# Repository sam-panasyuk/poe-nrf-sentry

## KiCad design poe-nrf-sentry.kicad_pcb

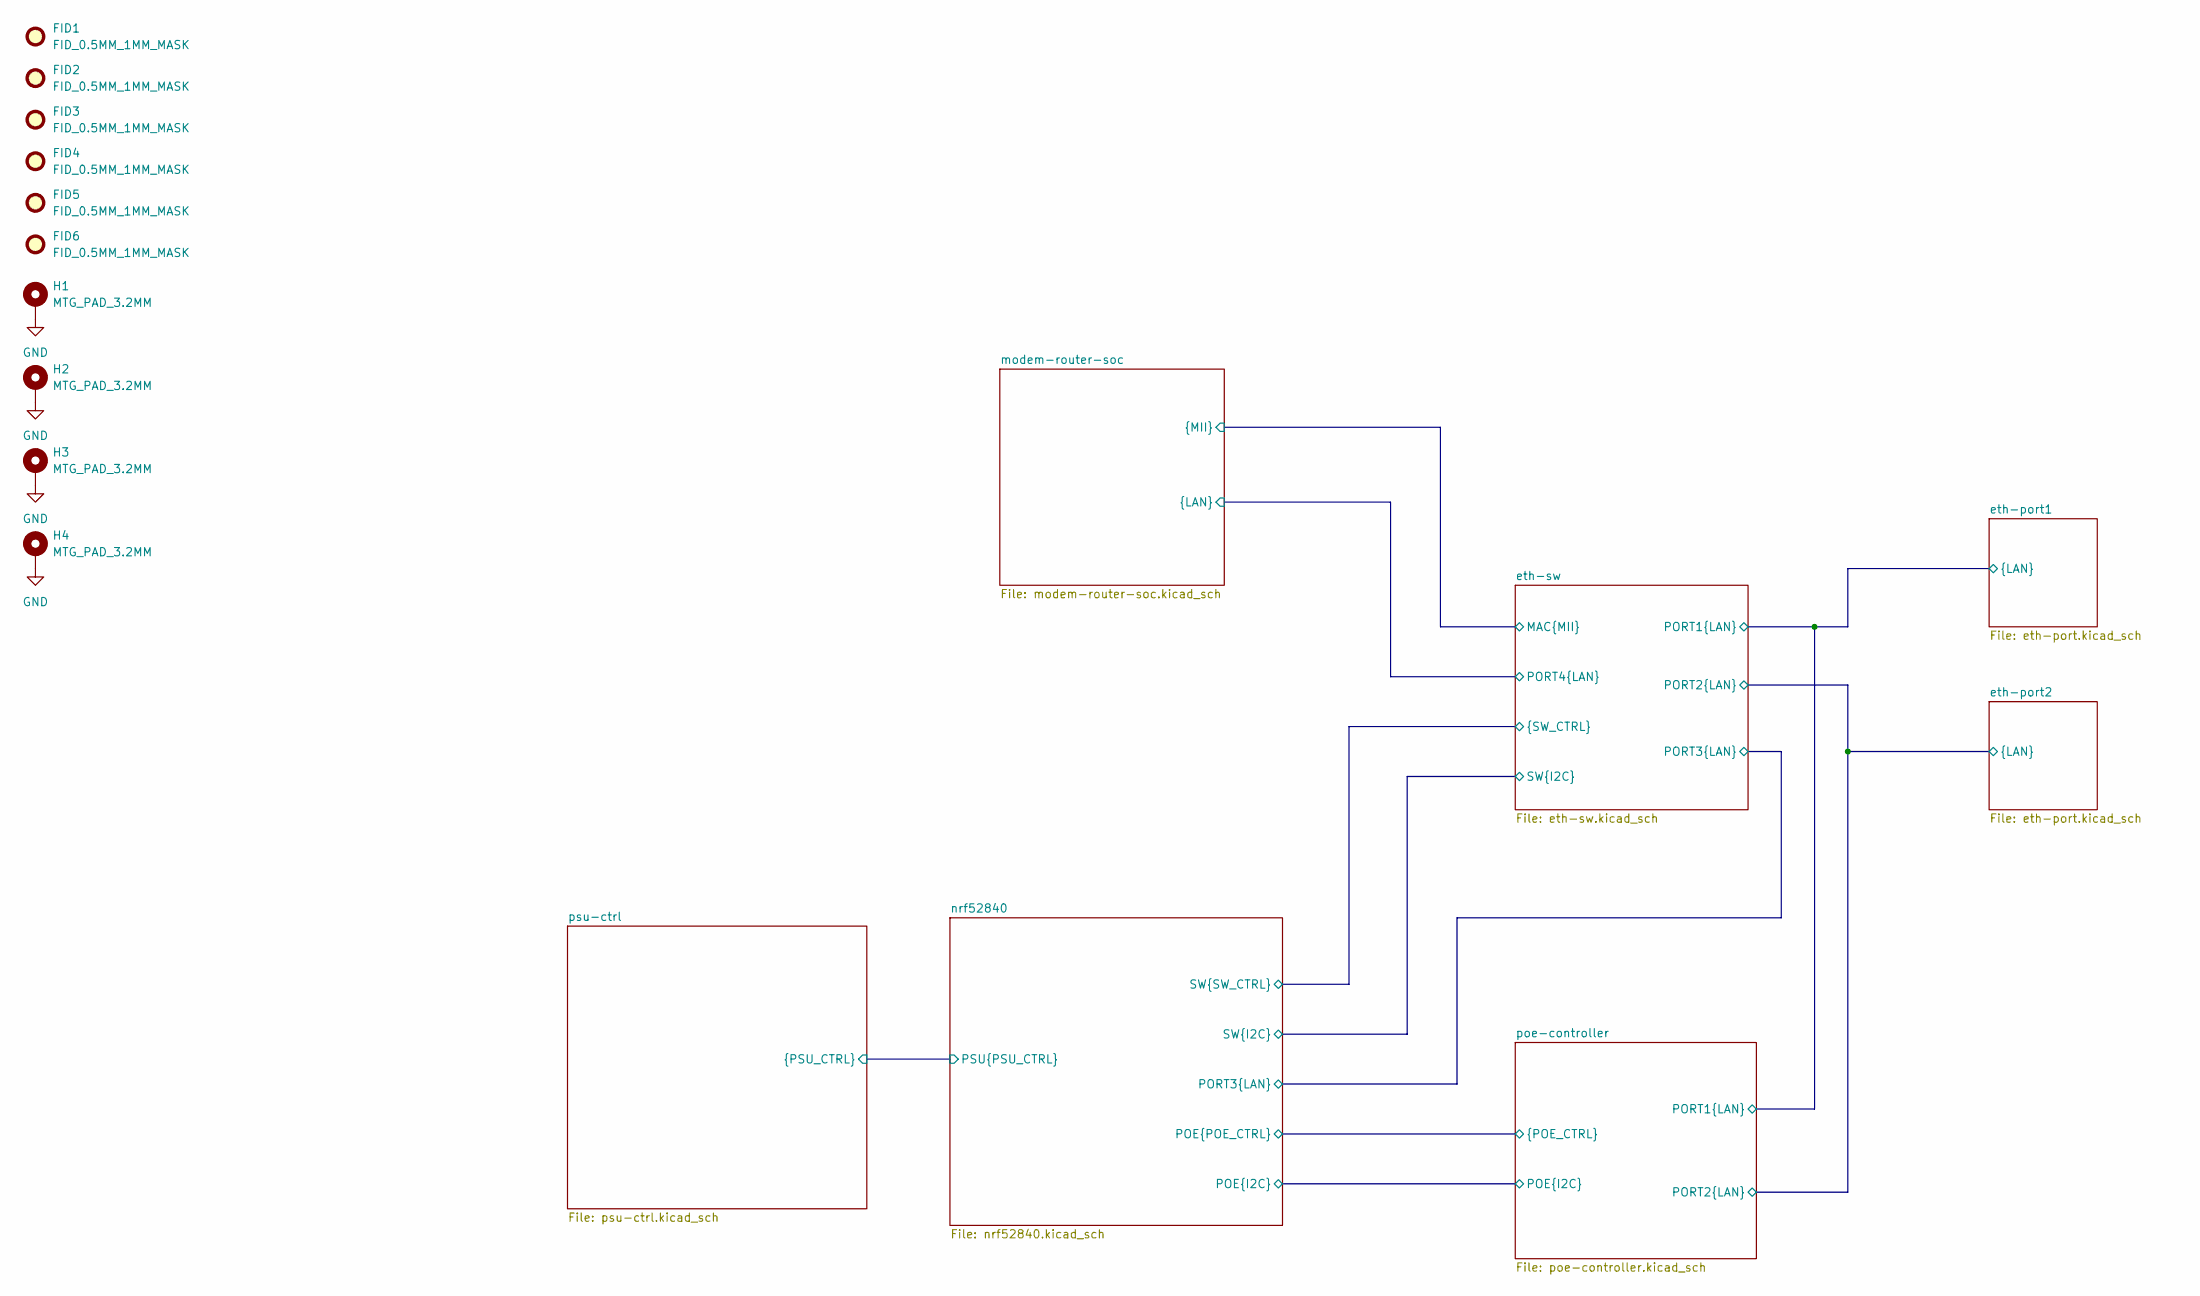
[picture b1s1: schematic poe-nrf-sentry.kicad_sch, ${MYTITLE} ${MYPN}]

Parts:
FID1, FID2, FID3, FID4, FID5, FID6: FID_0.5MM_1MM_MASK; Fiducial_0.5mm_Mask1mm
H1, H2, H3, H4: MTG_PAD_3.2MM; MountingHole_3.2mm_M3_Pad_TopBottom

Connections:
GND: H1.1 (1_1), H2.1 (1_1), H3.1 (1_1), H4.1 (1_1); also elsewhere on the board

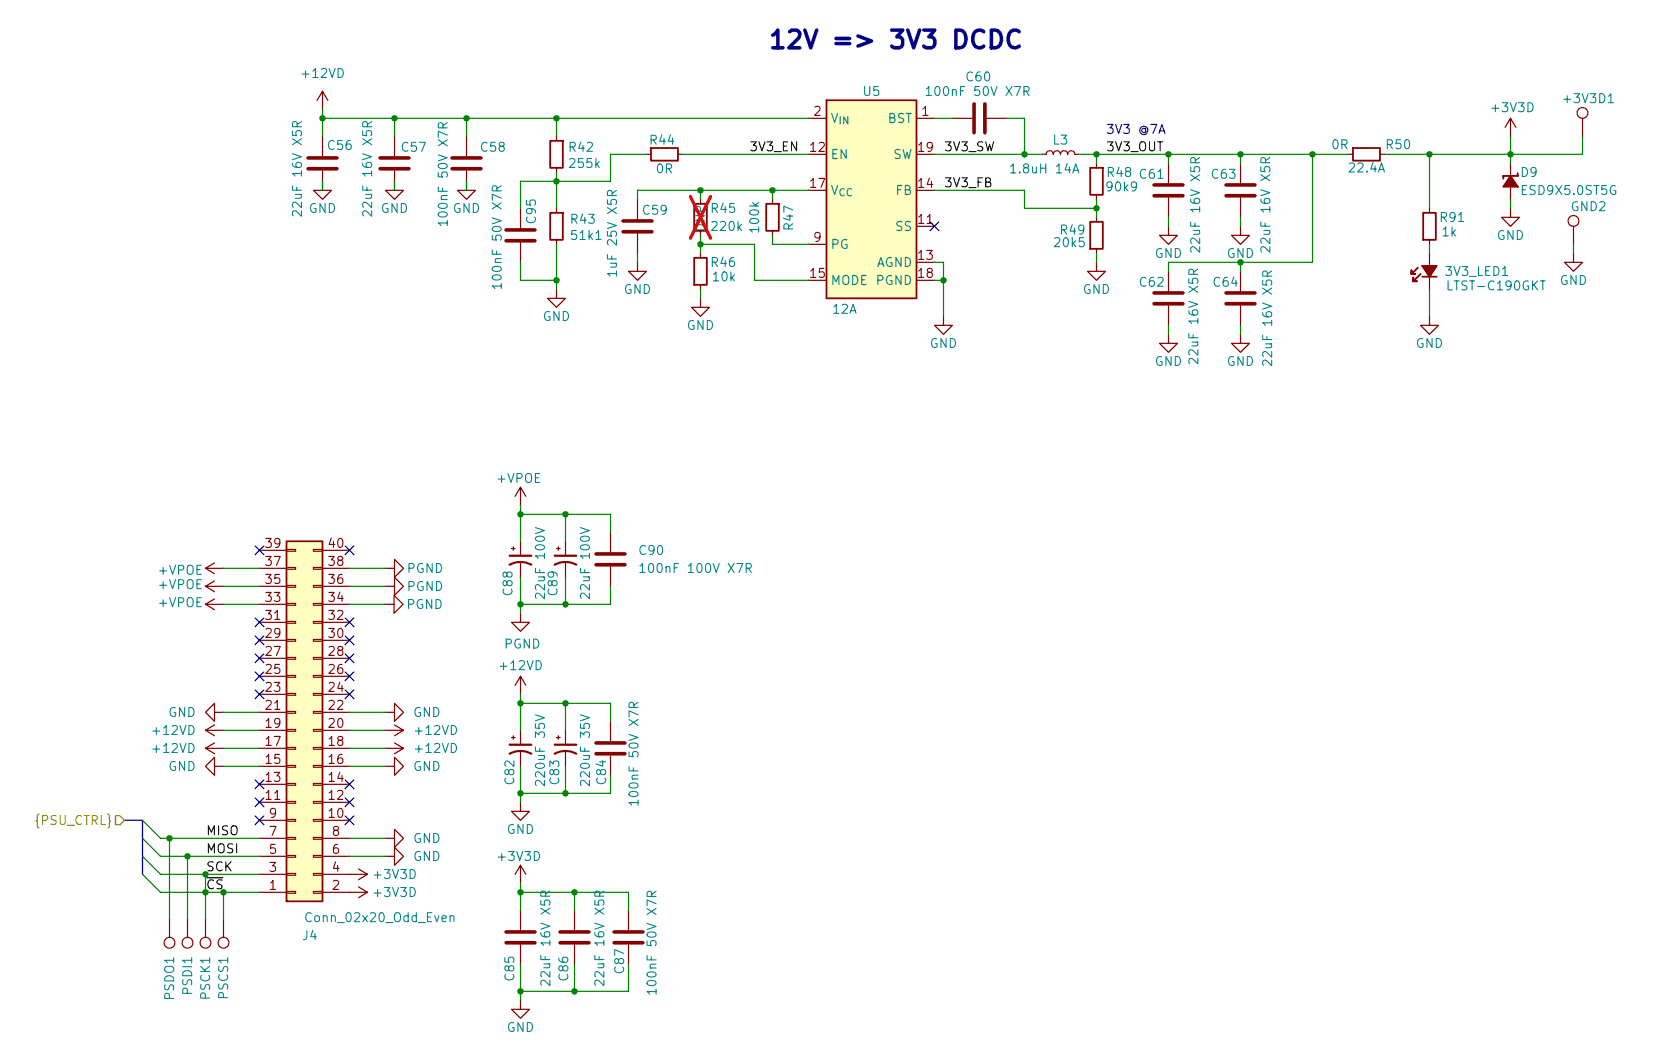
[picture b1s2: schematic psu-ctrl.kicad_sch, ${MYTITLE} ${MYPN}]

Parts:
3V3_LED1: LTST-C190GKT; LED_0603_1608Metric_G; MPN LTST-C190GKT
+3V3D1: TestPoint_1mm_0.5mm_TH; TestPoint_THTPad_D1.0mm_Drill0.5mm
C56, C57, C61, C62, C63, C64, C85, C86: 22uF 16V X5R; C_0603_1608Metric; MPN CL10A226MO7JZNC
C58, C60, C84, C87, C95: 100nF 50V X7R; C_0402_1005Metric; MPN CC0402KRX7R9BB104; JLCPN C131394
C59: 1uF 25V X5R; C_0402_1005Metric; MPN C1005X6S1A105K050BC
C82, C83: 220uF 35V; CP_Elec_8x10.5; MPN EMZA350ARA221MHA0G
C88, C89: 22uF 100V; CP_Elec_8x10.5; MPN UUX2A220MNL6GS
C90: 100nF 100V X7R; C_0603_1608Metric; MPN GRM188R72A104KA35D; JLCPN C113803
D9: ESD9X5.0ST5G; SOD-923; MPN ESD9X5.0ST5G
GND2: TestPoint_1mm_0.5mm_TH; TestPoint_THTPad_D1.0mm_Drill0.5mm
J4: Conn_02x20_Odd_Even; PinHeader_2x20_P2.54mm_Horizontal
L3: 1.8uH 14A; L_Coilcraft-XAL6030; MPN XAL6030-182MEC
PSCK1: TP 1mm; TestPoint_THTPad_D1.0mm_Drill0.5mm
PSCS1: TP 1mm; TestPoint_THTPad_D1.0mm_Drill0.5mm
PSDI1: TP 1mm; TestPoint_THTPad_D1.0mm_Drill0.5mm
PSDO1: TP 1mm; TestPoint_THTPad_D1.0mm_Drill0.5mm
R42: 255k; R_0402_1005Metric; MPN CR0402-FX-2553GLF
R43: 51k1; R_0402_1005Metric; MPN CR0402-FX-5112GLF
R44: 0R; R_0402_1005Metric; MPN ERJ2GE0R00X; JLCPN C17168
R45: R_220k_0402; R_0402_1005Metric; Tolerance 1%; MPN CR0402-FX-2203GLF; not fitted
R46: 10k; R_0402_1005Metric; MPN CR0402-FX-1002GLF; JLCPN C25744
R47: 100k; R_0402_1005Metric; MPN CRCW0402100KFKED
R48: 90k9; R_0402_1005Metric; MPN CR0402-FX-9092GLF
R49: 20k5; R_0402_1005Metric; MPN CRCW040220K0FKED
R50: R_0R_22.4A_0603; R_0603_1608Metric; Tolerance template_tolerance; MPN PMR03EZPJ000
R91: 1k; R_0402_1005Metric; MPN CR0402-FX-1001GLF
U5: 12A; QFN-20-1EP_3x3mm_P0.45mm_TPS56xxxx; MPN TPS56C230RJER

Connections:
+3V3D: +3V3D1.1 (1_1), C85.1, C86.1, C87.1, D9.1 (C), J4.2, J4.4, R50.2, R91.2; also elsewhere on the board
+12VD: C56.2, C57.2, C58.1, C82.1, C83.1, C84.1, J4.17, J4.18, J4.19, J4.20, R42.1, U5.2 (V_{IN}), U5.3 (V_{IN}), U5.4 (V_{IN}), U5.5 (V_{IN}); also elsewhere on the board
+VPOE: C88.1, C89.1, C90.1, J4.33, J4.35, J4.37; also elsewhere on the board
/eth-sw/MISO: J4.7, PSDO1.1 (1_1); also elsewhere on the board
/eth-sw/MOSI: J4.5, PSDI1.1 (1_1); also elsewhere on the board
/psu-ctrl/3V3_EN: R44.2, U5.12 (EN)
/psu-ctrl/3V3_FB: R48.2, R49.2, U5.14 (FB)
/psu-ctrl/3V3_OUT: C61.2, C62.2, C63.2, C64.2, L3.2, R48.1, R50.1
/psu-ctrl/3V3_SW: C60.1, L3.1, U5.6 (SW), U5.19 (SW), U5.20 (SW)
GND: 3V3_LED1.1 (C), C56.1, C57.1, C58.2, C59.1, C61.1, C62.1, C63.1, C64.1, C82.2, C83.2, C84.2, C85.2, C86.2, C87.2, C95.2, D9.2 (A), GND2.1 (1_1), J4.6, J4.8, J4.15, J4.16, J4.21, J4.22, R43.2, R46.1, R49.1, U5.7 (PGND), U5.8 (PGND), U5.13 (AGND), U5.18 (PGND), U5.21 (PGND); also elsewhere on the board
unnamed: 3V3_LED1.2 (A), R91.1
unnamed: C95.1, R42.2, R43.1, R44.1
unnamed: C60.2, U5.1 (BST)
unnamed: R45.1, R46.2, U5.15 (MODE)
unnamed: R47.2, U5.9 (PG)
unnamed: C59.2, R45.2, R47.1, U5.17 (V_{CC})
PGND: C88.2, C89.2, C90.2, J4.34, J4.36, J4.38; also elsewhere on the board

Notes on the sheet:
12V => 3V3 DCDC
3V3 @7A

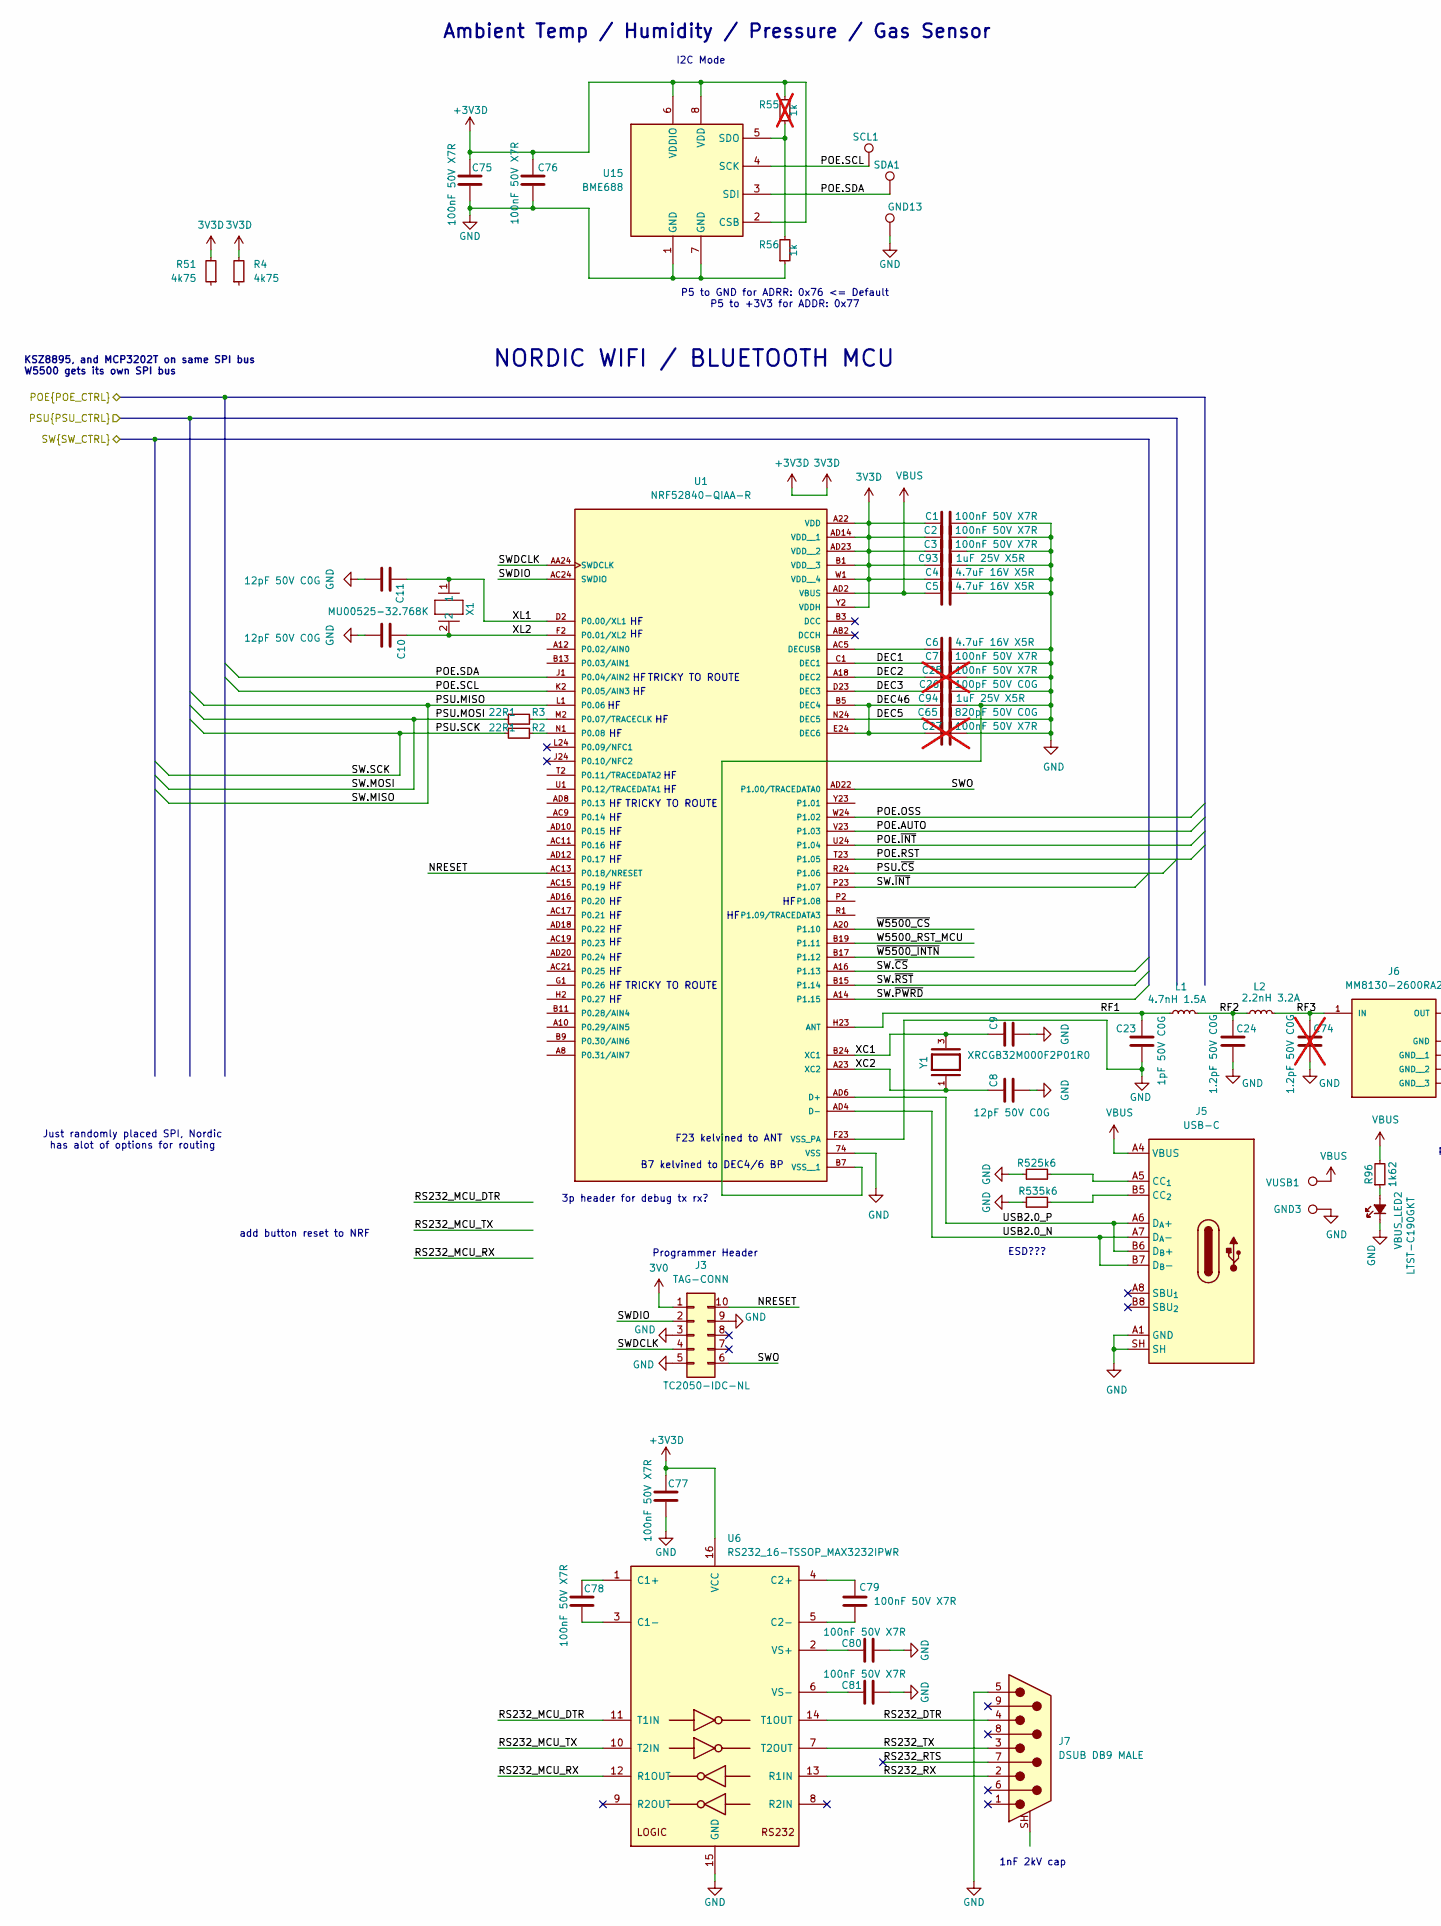
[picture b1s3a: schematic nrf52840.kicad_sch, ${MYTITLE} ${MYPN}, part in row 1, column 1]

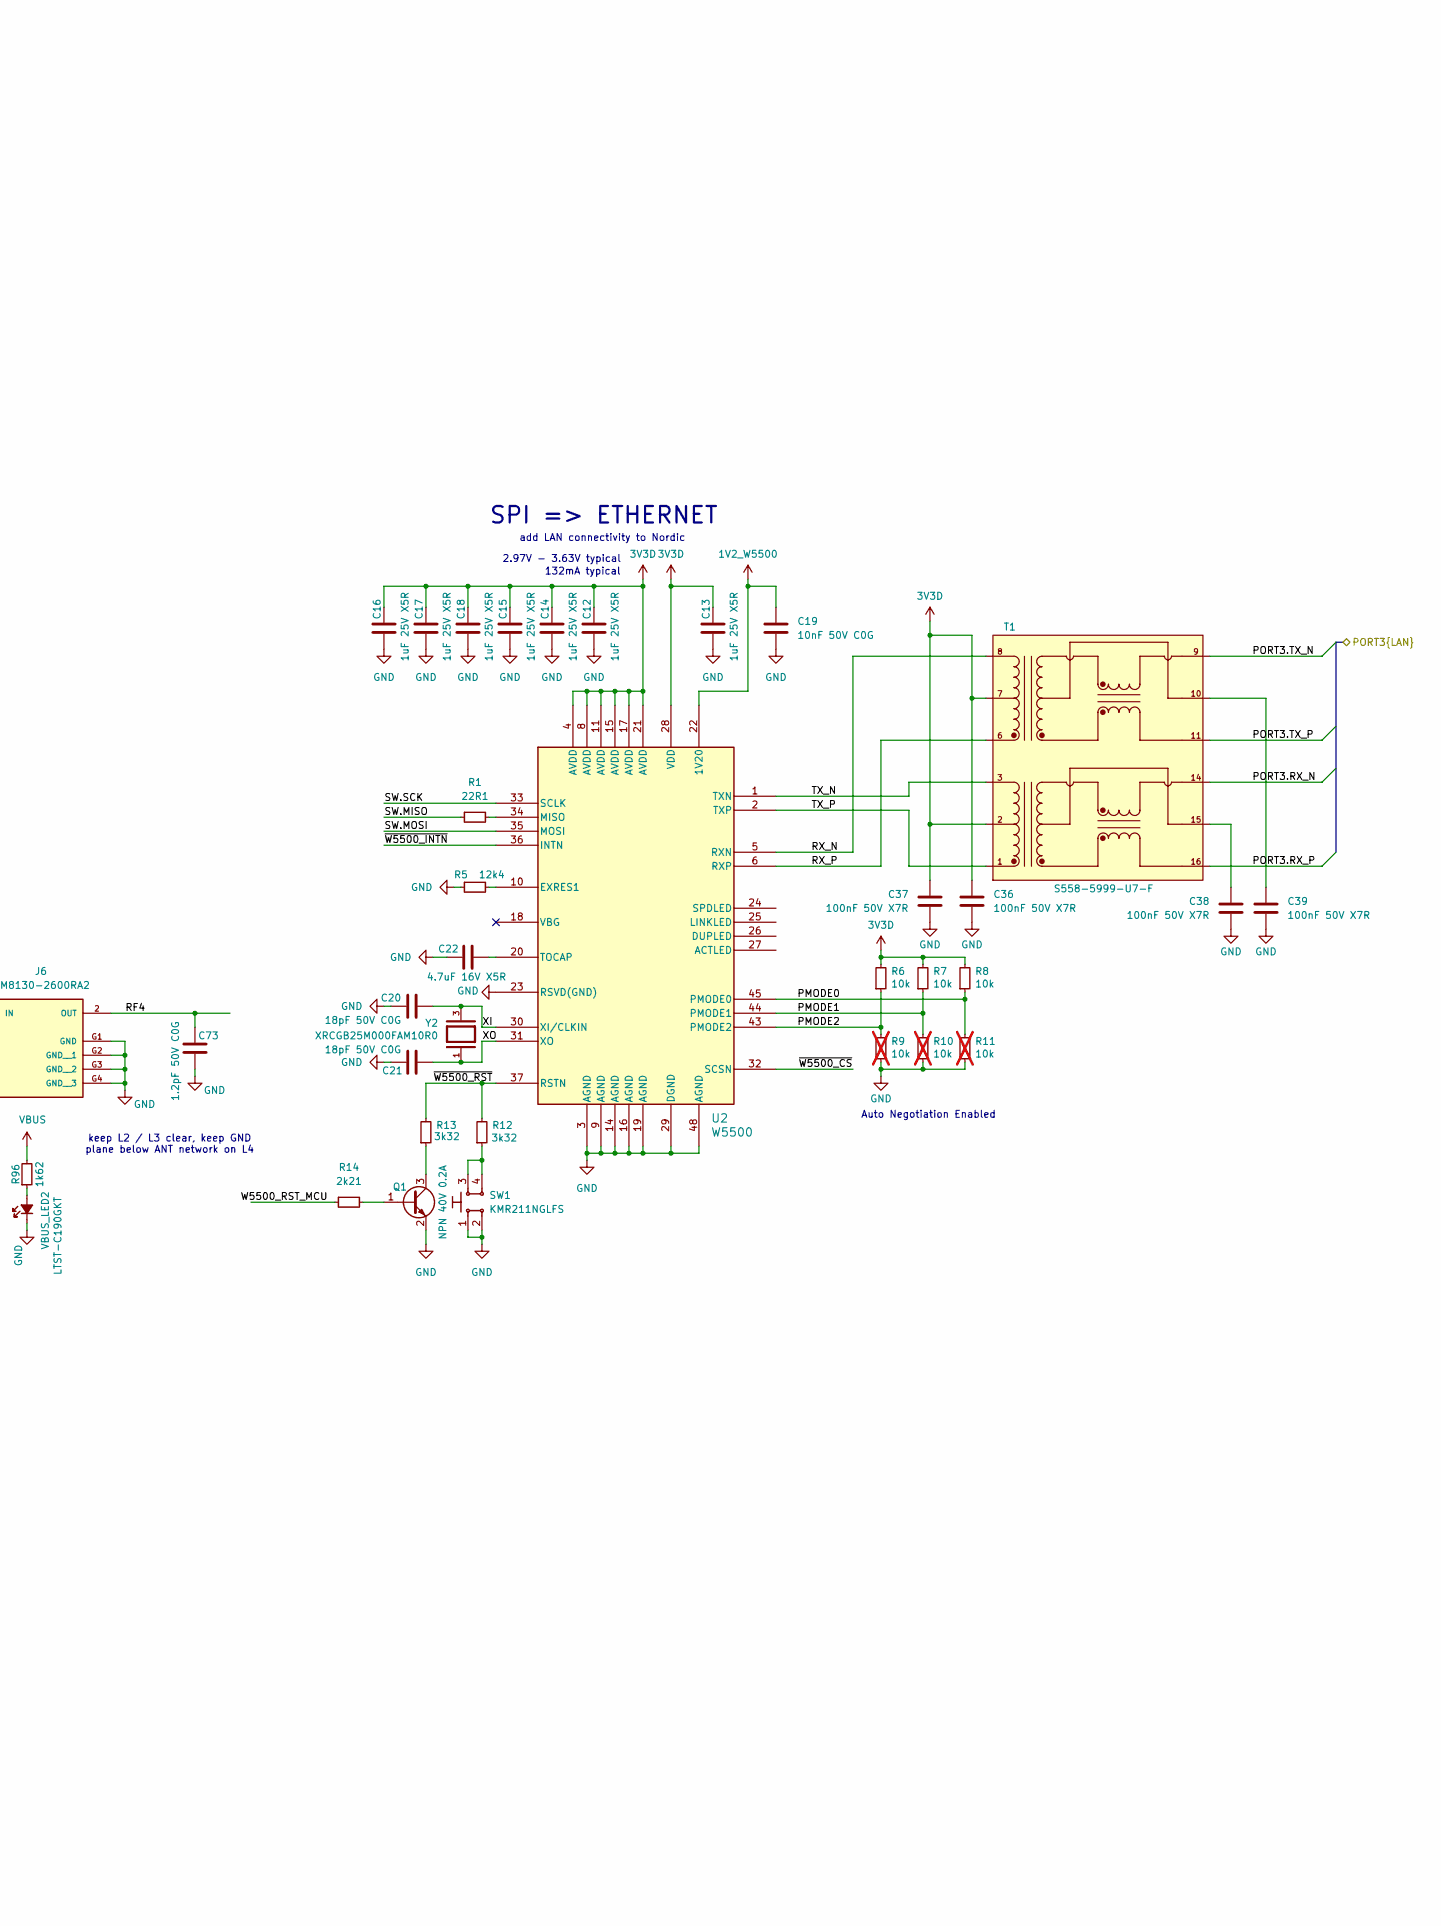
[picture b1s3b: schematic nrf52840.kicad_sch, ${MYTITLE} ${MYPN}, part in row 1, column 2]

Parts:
C1, C2, C3, C7, C36, C37, C38, C39, C75, C76, C77, C78, C79, C80, C81: 100nF 50V X7R; C_0402_1005Metric; MPN CC0402KRX7R9BB104; JLCPN C131394
C4, C5, C6, C22: 4.7uF 16V X5R; C_0402_1005Metric
C8, C9, C10, C11: 12pF 50V C0G; C_0402_1005Metric
C12, C13, C14, C15, C16, C17, C18, C93, C94: 1uF 25V X5R; C_0402_1005Metric; JLCPN C52923
C19: 10nF 50V C0G; C_0603_1608Metric
C20, C21: 18pF 50V C0G; C_0402_1005Metric
C23: 1pF 50V C0G; C_0402_1005Metric
C24, C73: 1.2pF 50V C0G; C_0402_1005Metric
C25, C27: 100nF 50V X7R; C_0402_1005Metric; MPN CC0402KRX7R9BB104; JLCPN C131394; not fitted
C26: 100pF 50V C0G; C_0402_1005Metric
C65: 820pF 50V C0G; C_0402_1005Metric
C74: 1.2pF 50V C0G; C_0402_1005Metric; not fitted
GND3: TestPoint_1.5mm_0.7mm_TH; TestPoint_THTPad_D1.5mm_Drill0.7mm
GND13: TestPoint_1mm_0.5mm_TH; TestPoint_THTPad_D1.0mm_Drill0.5mm
J3: TAG-CONN; Tag-Connect_TC2050-IDC-NL_2x5_P1.27mm; MPN TC2050-IDC-NL
J5: USB-C; USB-C_Receptacle_GCT_USB4105-GF-A; MPN USB4105-GF-A; JLCPN C5184243
J6: MM8130-2600RA2; MURATA_MM8130-2600RA2; MPN MM8130-2600RA2; JLCPN C167503
J7: DSUB DB9 MALE; DSUB-9_Pins_Horizontal_P2.77x2.84mm_EdgePinOffset7.70mm_Hou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; MPN A-DS 09 A/KG-T2S; JLCPN C7498157
L1: 4.7nH 1.5A; L_0603_1608Metric; MPN LQW18AN4N7B80D
L2: 2.2nH 3.2A; L_0603_1608Metric; MPN LQW18AN2N2C80D
Q1: NPN 40V 0.2A; SOT-323_SC-70; MPN MMBT3904WT1G; JLCPN C58011
R1, R2, R3: 22R1; R_0402_1005Metric; JLCPN C59651
R4, R51: 4k75; R_0402_1005Metric
R5: 12k4; R_0402_1005Metric
R6, R7, R8: 10k; R_0402_1005Metric; MPN CR0402-FX-1002GLF; JLCPN C25744
R9, R10, R11: 10k; R_0402_1005Metric; MPN CR0402-FX-1002GLF; JLCPN C25744; not fitted
R12, R13: 3k32; R_0402_1005Metric; JLCPN C60075
R14: 2k21; R_0402_1005Metric; JLCPN C324924
R52, R53: 5k6; R_0402_1005Metric; MPN RC0402FR-075K6L; JLCPN C25908
R55: 1k; R_0402_1005Metric; MPN CR0402-FX-1001GLF; not fitted
R56: 1k; R_0402_1005Metric; MPN CR0402-FX-1001GLF
R96: 1k62; R_0402_1005Metric; JLCPN C138038
SCL1: TestPoint_1mm_0.5mm_TH; TestPoint_THTPad_D1.0mm_Drill0.5mm
SDA1: TestPoint_1mm_0.5mm_TH; TestPoint_THTPad_D1.0mm_Drill0.5mm
SW1: SW_KMR211NGLFS_SMD; MPN KMR211NGLFS
T1: S558-5999-U7-F; Transformer_Ethernet_CNDtek_H1102N; MPN S558-5999-U7-F; JLCPN C6801130
U1: NRF52840-QIAA-R; XCVR_NRF52840-QIAA-R; MPN NRF52840-QIAA-R; JLCPN C190794
U2: W5500; LQFP-48_7x7mm_P0.5mm; MPN W5500; JLCPN C32843
U6: RS232_16-TSSOP_MAX3232IPWR; TSSOP-16_4.4x5mm_P0.65mm; MPN MAX3232IPWR; JLCPN C113205
U15: BME688; Bosch_LGA-8_3x3mm_P0.8mm_ClockwisePinNumbering; MPN BME688
VBUS_LED2: LTST-C190GKT; LED_0603_1608Metric_G; MPN LTST-C190GKT; JLCPN C125093
VUSB1: TestPoint_1.5mm_0.7mm_TH; TestPoint_THTPad_D1.5mm_Drill0.7mm
X1: MU00525-32.768K; XTAL_MU00525_NDK; MPN MU00525-32.768K
Y1: XRCGB32M000F2P01R0; XRCGB25M000FAM10R0; MPN XRCGB32M000F2P01R0; JLCPN C1985928
Y2: XRCGB25M000FAM10R0; MPN XRCGB25M000FAM10R0

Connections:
1V2_W5500: C19.1, U2.22 (1V20)
3V0: J3.1
+3V3D: C1.1, C2.1, C3.1, C4.1, C12.1, C13.1, C14.1, C15.1, C16.1, C17.1, C18.1, C36.1, C37.1, C75.2, C76.2, C77.2, C93.1, R4.2, R6.2, R7.2, R8.2, R51.2, R55.2, T1.2, T1.7, U1.A22 (VDD), U1.AD14 (VDD__1), U1.AD23 (VDD__2), U1.B1 (VDD__3), U1.W1 (VDD__4), U1.Y2 (VDDH), U2.4 (AVDD), U2.8 (AVDD), U2.11 (AVDD), U2.15 (AVDD), U2.17 (AVDD), U2.21 (AVDD), U2.28 (VDD), U6.16 (VCC), U15.2 (CSB), U15.6 (VDDIO), U15.8 (VDD); also elsewhere on the board
/eth-sw/MISO: R1.1, U1.L1 (P0.06); also elsewhere on the board
/eth-sw/MOSI: R2.1, U2.35 (MOSI); also elsewhere on the board
/eth-sw/PORT3.RX_N: T1.14; also elsewhere on the board
/eth-sw/PORT3.RX_P: T1.16; also elsewhere on the board
/eth-sw/PORT3.TX_N: T1.9; also elsewhere on the board
/eth-sw/PORT3.TX_P: T1.11; also elsewhere on the board
/eth-sw/~CS: U1.A16 (P1.13); also elsewhere on the board
/eth-sw/~INT: U1.P23 (P1.07); also elsewhere on the board
/eth-sw/~PWRD: U1.A14 (P1.15); also elsewhere on the board
/eth-sw/~RST: U1.B15 (P1.14); also elsewhere on the board
/nrf52840/DEC1: C7.1, U1.C1 (DEC1)
/nrf52840/DEC2: C25.1, U1.A18 (DEC2)
/nrf52840/DEC3: C26.1, U1.D23 (DEC3)
/nrf52840/DEC5: C65.1, U1.N24 (DEC5)
/nrf52840/DEC46: C27.1, C94.1, U1.B5 (DEC4), U1.E24 (DEC6)
/nrf52840/NRESET: J3.10, U1.AC13 (P0.18/NRESET)
/nrf52840/PMODE0: R8.1, R11.2, U2.45 (PMODE0)
/nrf52840/PMODE1: R7.1, R10.2, U2.44 (PMODE1)
/nrf52840/PMODE2: R6.1, R9.2, U2.43 (PMODE2)
/nrf52840/POE.AUTO: U1.V23 (P1.03); also elsewhere on the board
/nrf52840/POE.OSS: U1.W24 (P1.02); also elsewhere on the board
/nrf52840/POE.RST: U1.T23 (P1.05); also elsewhere on the board
/nrf52840/POE.SCL: SCL1.1 (1_1), U1.K2 (P0.05/AIN3), U15.4 (SCK); also elsewhere on the board
/nrf52840/POE.SDA: SDA1.1 (1_1), U1.J1 (P0.04/AIN2), U15.3 (SDI); also elsewhere on the board
/nrf52840/POE.~INT: U1.U24 (P1.04); also elsewhere on the board
/nrf52840/RF1: C23.1, L1.1, U1.H23 (ANT)
/nrf52840/RF2: C24.1, L1.2, L2.1
/nrf52840/RF3: C74.1, J6.1 (IN), L2.2
/nrf52840/RF4: C73.1, J6.2 (OUT)
/nrf52840/RS232_DTR: J7.4, U6.14 (T1OUT)
/nrf52840/RS232_MCU_DTR: U6.11 (T1IN)
/nrf52840/RS232_MCU_RX: U6.12 (R1OUT)
/nrf52840/RS232_MCU_TX: U6.10 (T2IN)
/nrf52840/RS232_RTS: J7.7
/nrf52840/RS232_RX: J7.2, U6.13 (R1IN)
/nrf52840/RS232_TX: J7.3, U6.7 (T2OUT)
/nrf52840/RX_N: T1.8, U2.5 (RXN)
/nrf52840/RX_P: T1.6, U2.6 (RXP)
/nrf52840/SWDCLK: J3.4, U1.AA24 (SWDCLK)
/nrf52840/SWDIO: J3.2, U1.AC24 (SWDIO)
/nrf52840/SWO: J3.6, U1.AD22 (P1.00/TRACEDATA0)
/nrf52840/TX_N: T1.3, U2.1 (TXN)
/nrf52840/TX_P: T1.1, U2.2 (TXP)
/nrf52840/USB2.0_N: J5.A7 (D_{A}-), J5.B7 (D_{B}-), U1.AD4 (D-)
/nrf52840/USB2.0_P: J5.A6 (D_{A}+), J5.B6 (D_{B}+), U1.AD6 (D+)
/nrf52840/W5500_RST_MCU: R14.1, U1.B19 (P1.11)
/nrf52840/XC1: C9.1, U1.B24 (XC1), Y1.3
/nrf52840/XC2: C8.1, U1.A23 (XC2), Y1.1
/nrf52840/XI: C20.2, U2.30 (XI/CLKIN), Y2.3
/nrf52840/XL1: C11.1, U1.D2 (P0.00/XL1), X1.1
/nrf52840/XL2: C10.1, U1.F2 (P0.01/XL2), X1.2
/nrf52840/XO: C21.2, U2.31 (XO), Y2.1
/nrf52840/~W5500_CS: U1.A20 (P1.10), U2.32 (SCSN)
/nrf52840/~W5500_INTN: U1.B17 (P1.12), U2.36 (INTN)
/nrf52840/~W5500_RST: R12.2, R13.2, U2.37 (RSTN)
GND: C1.2, C2.2, C3.2, C4.2, C5.2, C6.2, C7.2, C8.2, C9.2, C10.2, C11.2, C12.2, C13.2, C14.2, C15.2, C16.2, C17.2, C18.2, C19.2, C20.1, C21.1, C22.1, C23.2, C24.2, C25.2, C26.2, C27.2, C36.2, C37.2, C38.2, C39.2, C65.2, C73.2, C74.2, C75.1, C76.1, C77.1, C80.2, C81.2, C93.2, C94.2, GND3.1 (1_1), GND13.1 (1_1), J3.3, J3.5, J3.9, J5.A1 (GND), J5.A12 (GND), J5.B1 (GND), J5.B12 (GND), J5.SH, J6.G1 (GND), J6.G2 (GND__1), J6.G3 (GND__2), J6.G4 (GND__3), J7.5, Q1.2 (E), R5.1, R9.1, R10.1, R11.1, R52.1, R53.1, R56.1, SW1.1, SW1.2, U1.74 (VSS), U1.B7 (VSS__1), U1.F23 (VSS_PA), U2.3 (AGND), U2.9 (AGND), U2.14 (AGND), U2.16 (AGND), U2.19 (AGND), U2.23 (RSVD(GND)), U2.29 (DGND), U2.42 (RSVD), U2.48 (AGND), U6.15 (GND), U15.1 (GND), U15.7 (GND), VBUS_LED2.1 (C); also elsewhere on the board
unnamed: C38.1, T1.15
unnamed: C39.1, T1.10
unnamed: J5.A5 (CC_{1}), R52.2
unnamed: J5.B5 (CC_{2}), R53.2
unnamed: Q1.1 (B), R14.2
unnamed: Q1.3 (C), R13.1
unnamed: R12.1, SW1.3, SW1.4
unnamed: C6.1, U1.AC5 (DECUSB)
unnamed: R2.2, U1.M2 (P0.07/TRACECLK)
unnamed: R3.2, U1.N1 (P0.08)
unnamed: R5.2, U2.10 (EXRES1)
unnamed: R1.2, U2.34 (MISO)
unnamed: C22.2, U2.20 (TOCAP)
unnamed: C78.2, U6.1 (C1+)
unnamed: C78.1, U6.3 (C1-)
unnamed: C79.2, U6.4 (C2+)
unnamed: C79.1, U6.5 (C2-)
unnamed: C80.1, U6.2 (VS+)
unnamed: C81.1, U6.6 (VS-)
unnamed: R55.1, R56.2, U15.5 (SDO)
unnamed: R96.1, VBUS_LED2.2 (A)
VBUS: C5.1, J5.A4 (VBUS), J5.A9 (VBUS), J5.B4 (VBUS), J5.B9 (VBUS), R96.2, U1.AD2 (VBUS), VUSB1.1 (1_1)

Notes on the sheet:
P5 to GND for ADRR: 0x76 <= Default P5 to +3V3 for ADDR: 0x77
F23 kelvined to ANT
Just randomly placed SPI, Nordic has alot of options for routing
KSZ8895, and MCP3202T on same SPI bus W5500 gets its own SPI bus
add LAN connectivity to Nordic
I2C Mode
B7 kelvined to DEC4/6 BP
132mA typical
Auto Negotiation Enabled
TRICKY TO ROUTE
keep L2 / L3 clear, keep GND plane below ANT network on L4
SPI => ETHERNET
Programmer Header
NORDIC WIFI / BLUETOOTH MCU
Ambient Temp / Humidity / Pressure / Gas Sensor
3p header for debug tx rx?
add button reset to NRF
ESD???
2.97V - 3.63V typical
1nF 2kV cap

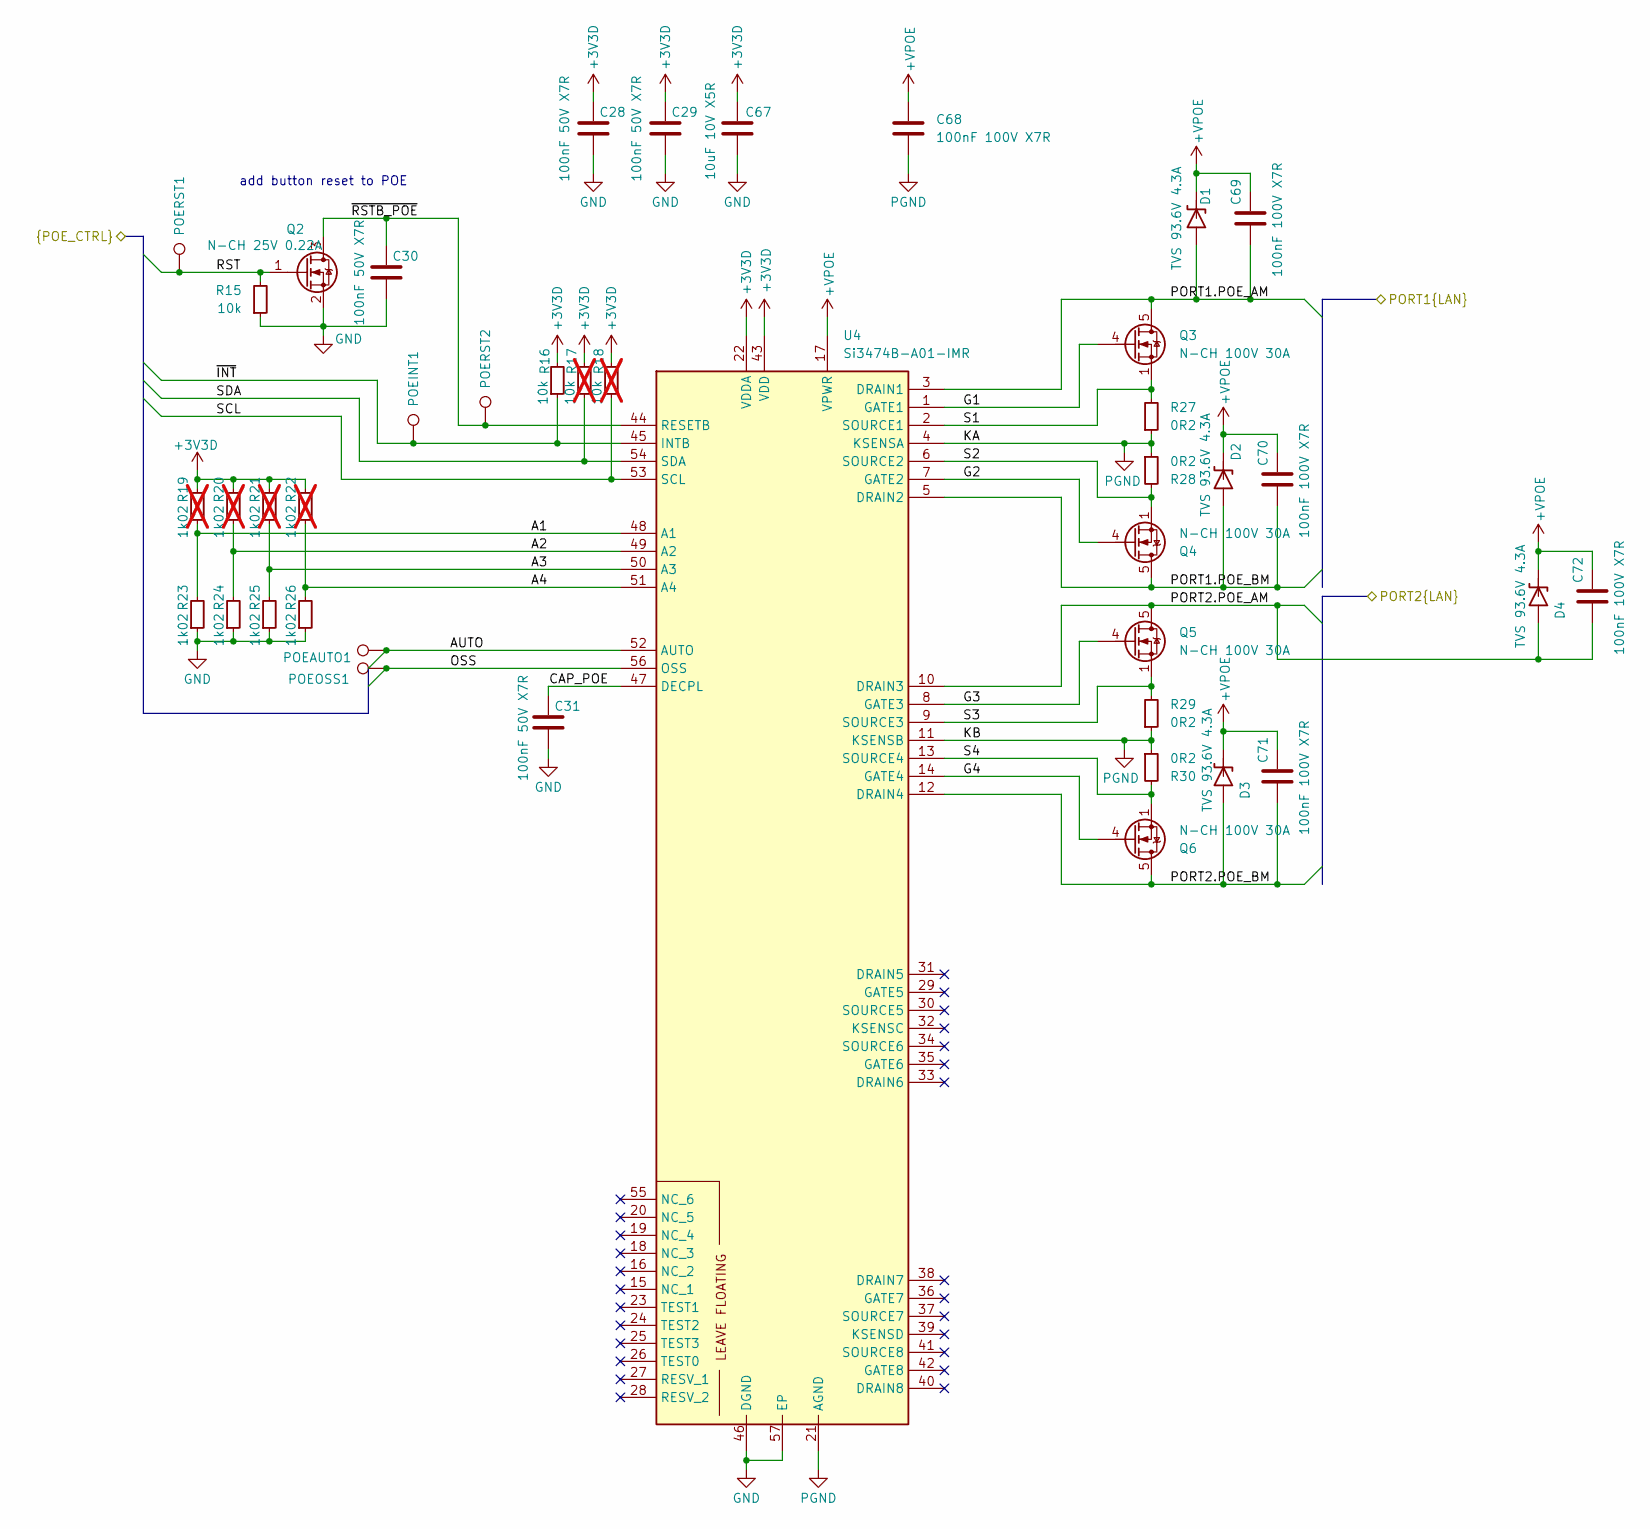
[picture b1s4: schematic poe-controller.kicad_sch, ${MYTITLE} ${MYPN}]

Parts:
C28, C29, C30, C31: 100nF 50V X7R; C_0402_1005Metric; MPN CC0402KRX7R9BB104; JLCPN C131394
C67: 10uF 10V X5R; C_0402_1005Metric
C68, C69, C70, C71, C72: 100nF 100V X7R; C_0603_1608Metric; MPN GRM188R72A104KA35D; JLCPN C113803
D1, D2, D3, D4: TVS 93.6V 4.3A; D_SMA; MPN SZ1SMA58CAT3G
POEAUTO1: TP 1mm; TestPoint_THTPad_D1.0mm_Drill0.5mm
POEINT1: TP 1mm; TestPoint_THTPad_D1.0mm_Drill0.5mm
POEOSS1: TP 1mm; TestPoint_THTPad_D1.0mm_Drill0.5mm
POERST1, POERST2: TP 1mm; TestPoint_THTPad_D1.0mm_Drill0.5mm
Q2: N-CH 25V 0.22A; FDV301N; MPN FDV301N
Q3, Q4, Q5, Q6: N-CH 100V 30A; LFPAK33; MPN PSMN040-100MSEX; JLCPN C458214
R15, R16: 10k; R_0402_1005Metric; MPN CR0402-FX-1002GLF; JLCPN C25744
R17, R18: 10k; R_0402_1005Metric; MPN CR0402-FX-1002GLF; JLCPN C25744; not fitted
R19, R20, R21, R22: 1k02; R_0402_1005Metric; MPN RC0402FR-071K02L; JLCPN C163485; not fitted
R23, R24, R25, R26: 1k02; R_0402_1005Metric; MPN RC0402FR-071K02L; JLCPN C163485
R27, R28, R29, R30: 0R2; R_1210_3225Metric
U4: Si3474B-A01-IMR; QFN50P800X800X90-57N; MPN Si3474B-A01-IMR

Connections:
+3V3D: C28.1, C29.1, C67.1, R16.2, R17.2, R18.2, R19.2, R20.2, R21.2, R22.2, U4.22 (VDDA), U4.43 (VDD); also elsewhere on the board
+VPOE: C68.1, C69.1, C70.1, C71.1, C72.1, D1.1 (C), D2.1 (C), D3.1 (C), D4.1 (C), U4.17 (VPWR); also elsewhere on the board
/eth-port1/POE_AM: C69.2, D1.2 (A), Q3.5 (D), U4.3 (DRAIN1); also elsewhere on the board
/eth-port1/POE_BM: C70.2, D2.2 (A), Q4.5 (D), U4.5 (DRAIN2); also elsewhere on the board
/eth-port2/POE_AM: C72.2, D4.2 (A), Q5.5 (D), U4.10 (DRAIN3); also elsewhere on the board
/eth-port2/POE_BM: C71.2, D3.2 (A), Q6.5 (D), U4.12 (DRAIN4); also elsewhere on the board
/nrf52840/POE.AUTO: POEAUTO1.1 (1_1), U4.52 (AUTO); also elsewhere on the board
/nrf52840/POE.OSS: POEOSS1.1 (1_1), U4.56 (OSS); also elsewhere on the board
/nrf52840/POE.RST: POERST1.1 (1_1), Q2.1 (G), R15.2; also elsewhere on the board
/nrf52840/POE.SCL: R18.1, U4.53 (SCL); also elsewhere on the board
/nrf52840/POE.SDA: R17.1, U4.54 (SDA); also elsewhere on the board
/nrf52840/POE.~INT: POEINT1.1 (1_1), R16.1, U4.45 (INTB); also elsewhere on the board
/poe-controller/A1: R19.1, R23.2, U4.48 (A1)
/poe-controller/A2: R20.1, R24.2, U4.49 (A2)
/poe-controller/A3: R21.1, R25.2, U4.50 (A3)
/poe-controller/A4: R22.1, R26.2, U4.51 (A4)
/poe-controller/CAP_POE: C31.1, U4.47 (DECPL)
/poe-controller/G1: Q3.4 (G), U4.1 (GATE1)
/poe-controller/G2: Q4.4 (G), U4.7 (GATE2)
/poe-controller/G3: Q5.4 (G), U4.8 (GATE3)
/poe-controller/G4: Q6.4 (G), U4.14 (GATE4)
/poe-controller/S1: Q3.1 (S), Q3.2 (S), Q3.3 (S), R27.2, U4.2 (SOURCE1)
/poe-controller/S2: Q4.1 (S), Q4.2 (S), Q4.3 (S), R28.2, U4.6 (SOURCE2)
/poe-controller/S3: Q5.1 (S), Q5.2 (S), Q5.3 (S), R29.2, U4.9 (SOURCE3)
/poe-controller/S4: Q6.1 (S), Q6.2 (S), Q6.3 (S), R30.2, U4.13 (SOURCE4)
/poe-controller/~RSTB_POE: C30.1, POERST2.1 (1_1), Q2.3 (D), U4.44 (RESETB)
GND: C28.2, C29.2, C30.2, C31.2, C67.2, Q2.2 (S), R15.1, R23.1, R24.1, R25.1, R26.1, U4.46 (DGND), U4.57 (EP); also elsewhere on the board
PGND: C68.2, R27.1, R28.1, R29.1, R30.1, U4.4 (KSENSA), U4.11 (KSENSB), U4.21 (AGND); also elsewhere on the board

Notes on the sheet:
add button reset to POE

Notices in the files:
parts and their libraries:
License: Apache-2.0
